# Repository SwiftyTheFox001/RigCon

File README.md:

# RigCon
Extension Board for the ClockworkPI uConsole to connect ham radio equiptment

## Features
- Rig Interface equal to the DigiRig
 - Audio interface + PTT (2,5mm Audio Jack)
 - UART interface (2,5mm Audio Jack)
- Additional external USB-C Port (500mA max)
- RTC with Backup Battery (CR1220)

## Production

### JLC PCB
The main PCB can be ordered nearly assembled via JLC PCB.
- PCB settings:
 - Load .zip file from the "Production" folder
 - PCB Thickness: 1mm
 - Surface Finish: ENIG (recommended because of the edge connector)
- Assembly:
 - use bom_JLC.csv and positions_JLC.csv from the  "Production" folder
 - Check rotation of chips THRICE! Rotate them so, that the pink dot is alligned with the white arrows.

### DigiKey
The battery clip, the two jacks and the USB port were ordered seperately from Digikey. See "Production/bom_complete.csv" for the product names or check in KiCAD directly.

These parts need to be soldered manually. Drop a bit of solder on the GND pin of the bettery clip to ensure that the pad is contacted properly.
 
## Setup the RTC
Follow the tutorial here: https://learn.adafruit.com/adding-a-real-time-clock-to-raspberry-pi/set-up-and-test-i2c
The used RTC is a pcf8523!

## Version History
### v1.1
Fixes of v1.0 applied to schematic, not re-ordered YET

Changes from RigCon version 1.0 to 1.1:
- changed clock crystal footprint
- removed I2C pullup resistor footprints (was DNP before)
- removed unneccessary load caps for clock crystal (RTC has internal ones)
- changed cap value on CM108B pin 37 to 10uF (NECESSARY!)
- removed GND connectrio on CM108B pin 16 SDIN (optional, simplified)

Added directory FrontPanel/ with dxf, openSCAD and stl files
Added Schematic to main dir
Added Render Pic of PCB to main dir

### v1.0
First ordered version.

## This work is based on other projects!
[DigiRig-mobile](https://github.com/softcomplex/Digirig-Mobile) ([v1.9](https://github.com/softcomplex/Digirig-Mobile/tree/6721ff3781d7879b822c3f6550d4fcae7a4c0a2a)) (GNU GPL v3)
To provide an audio, ptt and uart interface for digital modes for ham radio. The CM108 was replaced with an CM108B and the 2-port USB controller was replaced with a 4-port USB controller to accomodate the additional external USB Port. The pinout of the audio jacks, solder pads for configuration and test pins were reused 1:1 to allow an easy reuse of exisiting peripherals and support for a wide range of transceivers.

[uconsole-expansion-card-template-kicad](https://github.com/PotatoMania/uconsole-expansion-card-template-kicad) ([used Version](https://github.com/PotatoMania/uconsole-expansion-card-template-kicad/tree/a174627fb24a4a155137b862d881c7e6f08ff017)) (CC BY-SA 4.0) 
PCB Outline, speakers, M.2 connector and mounting hole placements. I Changed to shape of mounting holes and the speaker pads, but all measurements provided by the original were correct.

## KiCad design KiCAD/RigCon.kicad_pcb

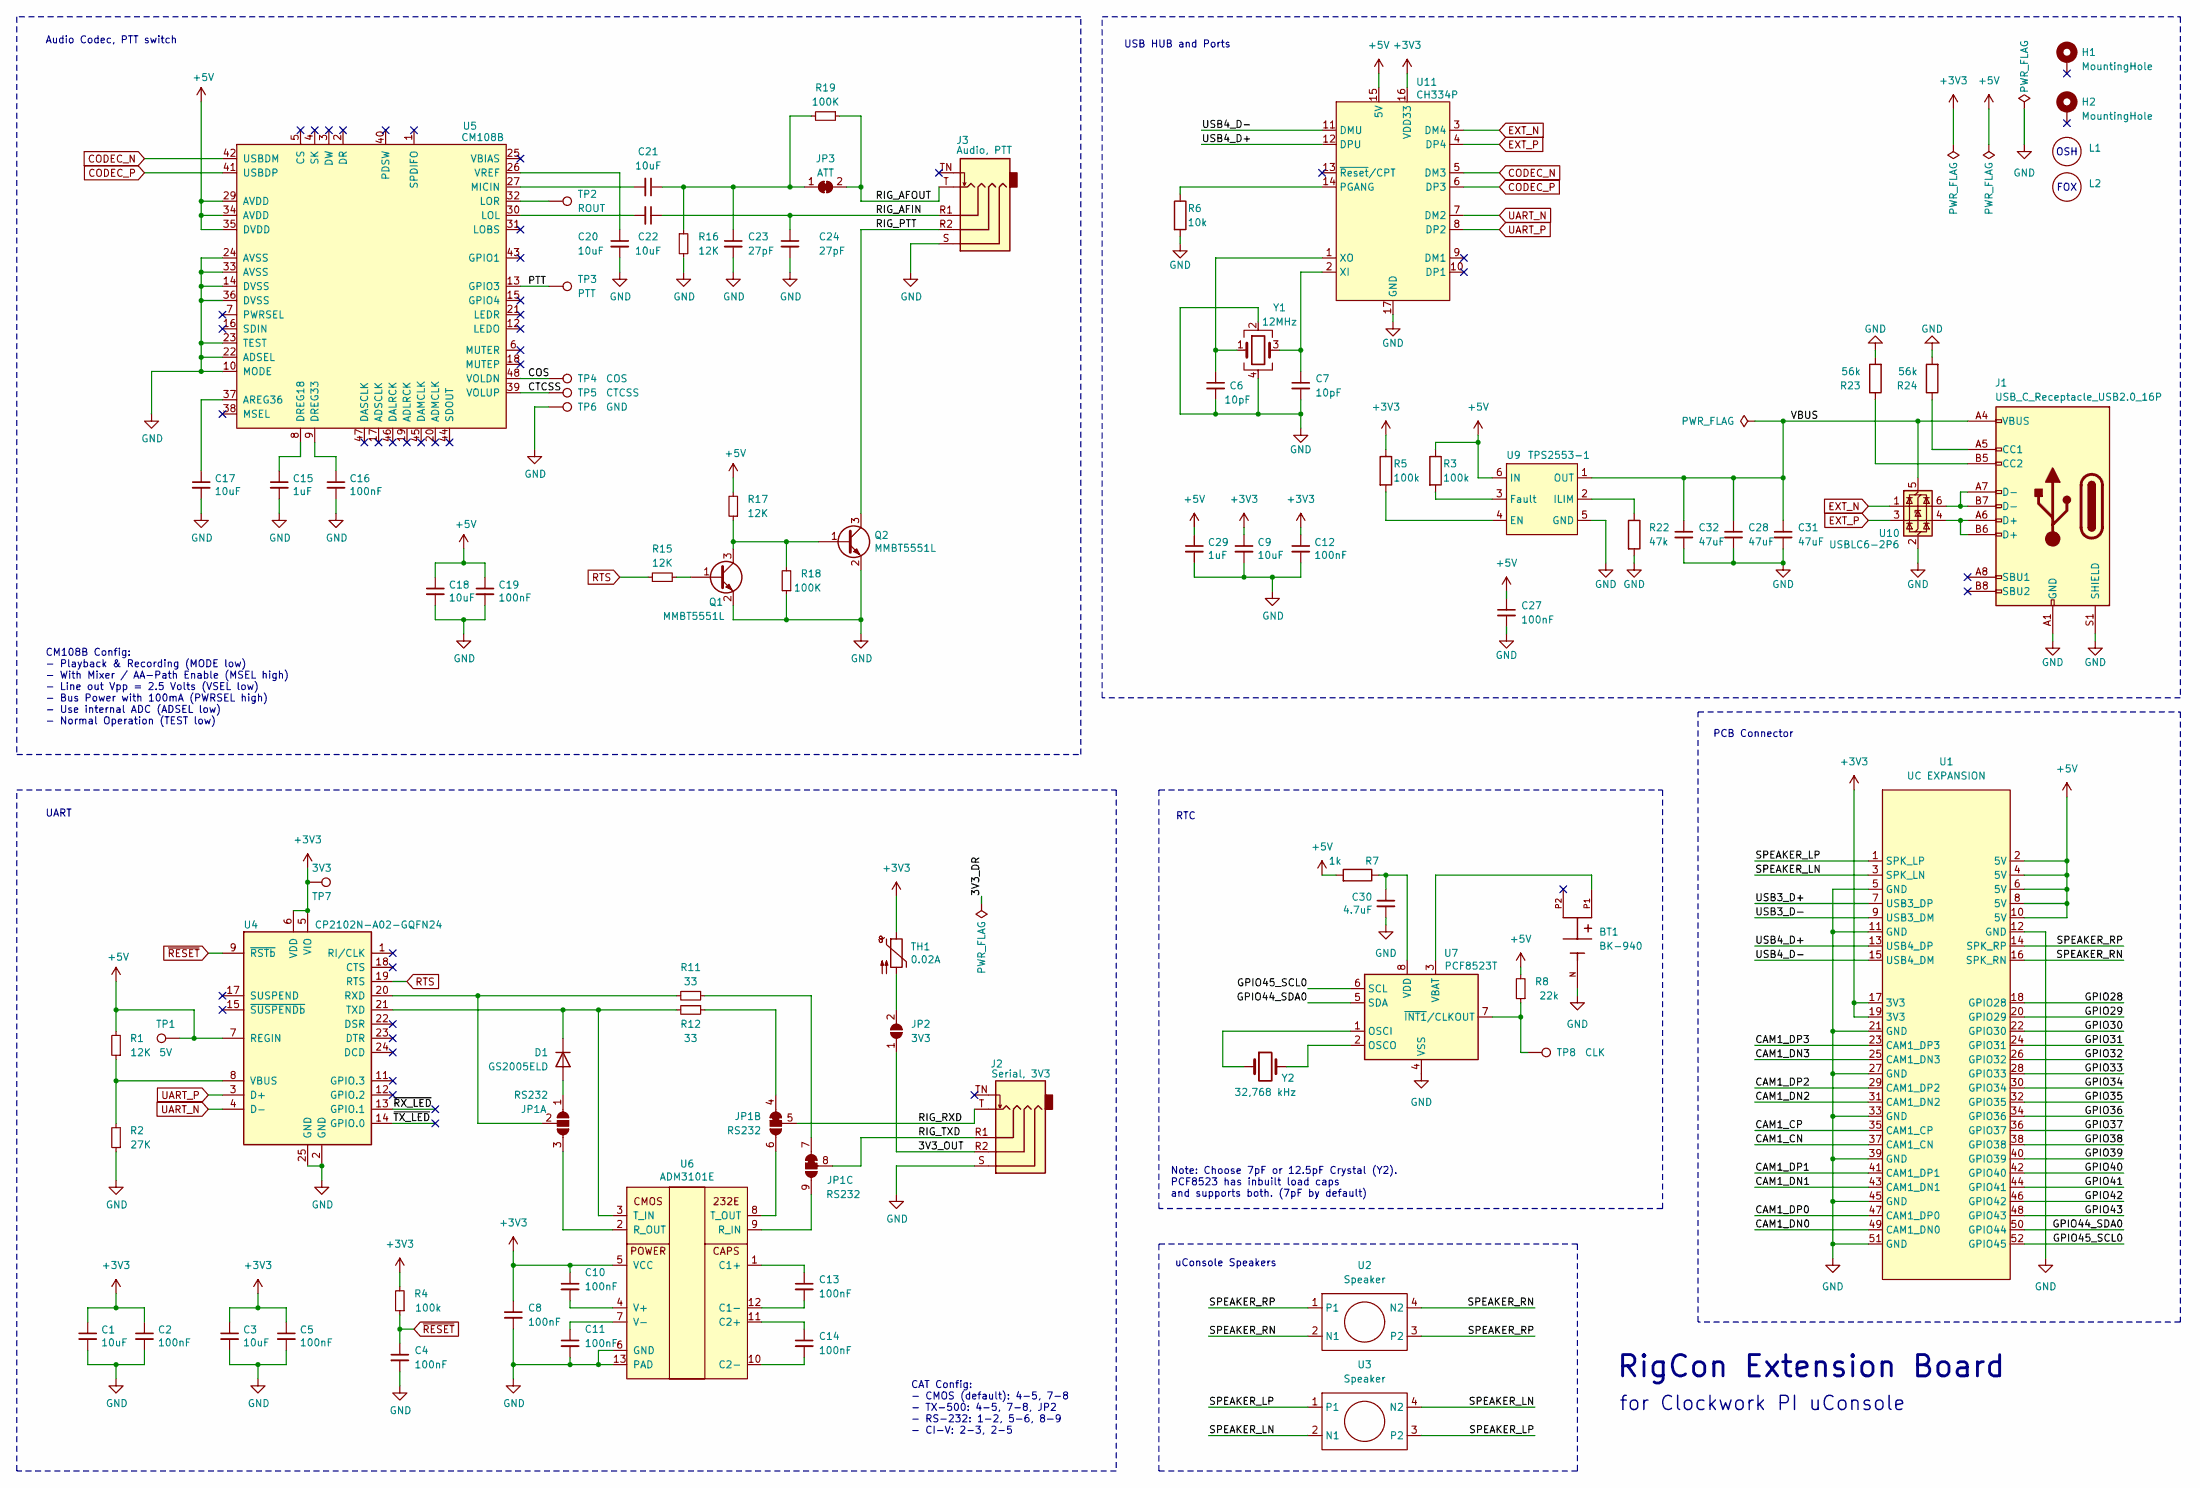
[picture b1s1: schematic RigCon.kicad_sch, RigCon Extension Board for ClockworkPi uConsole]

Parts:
BT1: BK-940; MPD_BK-940; PARTREV 04/15/21; DigiKeyNr BK-940
C1, C3, C9, C17, C18, C20, C21, C22: 10uF; C_0402_1005Metric; LCSC C15525
C2, C4, C5, C8, C10, C11, C12, C13, C14, C16, C19, C27: 100nF; C_0402_1005Metric; LCSC C1525
C6, C7: 10pF; C_0402_1005Metric; LCSC C1557
C15, C29: 1uF; C_0402_1005Metric; LCSC C52923
C23, C24: 27pF; C_0402_1005Metric; LCSC C1557
C28, C31, C32: 47uF; C_0805_2012Metric; LCSC C16780
C30: 4.7uF; C_0402_1005Metric; LCSC C23733
D1: GS2005ELD; D_SOD-923; LCSC C91106
H1, H2: MountingHole; MountingHole_5mm_Pad_Via
J1: USB_C_Receptacle_USB2.0_16P; USB-4520-03-X-A; DigiKeyNr USB4520-03-1-A
J2, J3: PJ-320A; SJ2-25774x-SMT; DigiKeyNr CP-SJ2-25774A-SMT
JP1: RS232; SolderJumper9-BCu
JP2: 3V3; SolderJumper2-BCu
JP3: ATT; SolderJumper-BCu-Bridged
L1: OSHW-Symbol_6.7x6mm_SilkScreen
L2: Logo_Fox
Q1, Q2: MMBT5551L; SOT-23; LCSC C41095
R1, R15, R16, R17: 12K; R_0402_1005Metric; LCSC C25752
R2: 27K; R_0402_1005Metric
R3, R4, R5: 100k; R_0402_1005Metric
R6: 10k; R_0402_1005Metric
R7: 1k; R_0402_1005Metric
R8: 22k; R_0402_1005Metric
R11, R12: 33; R_0402_1005Metric
R18, R19: 100K; R_0402_1005Metric
R22: 47k; R_0402_1005Metric
R23, R24: 56k; R_0402_1005Metric
TH1: 0.02A; R_0603_1608Metric; LCSC C914089
TP1: 5V; TestPoint_THTPad_D1.5mm_Drill0.7mm
TP2: ROUT; TestPoint_THTPad_D1.5mm_Drill0.7mm
TP3: PTT; TestPoint_THTPad_D1.5mm_Drill0.7mm
TP4: COS; TestPoint_THTPad_D1.5mm_Drill0.7mm
TP5: CTCSS; TestPoint_THTPad_D1.5mm_Drill0.7mm
TP6: GND; TestPoint_THTPad_D1.5mm_Drill0.7mm
TP7: 3V3; TestPoint_THTPad_D1.5mm_Drill0.7mm
TP8: CLK; TestPoint_THTPad_D1.5mm_Drill0.7mm
U1: UC EXPANSION; edge-minipcie
U2, U3: Speaker; speaker pads
U4: CP2102N-A02-GQFN24; QFN-24-1EP_4x4mm_P0.5mm_EP2.6x2.6mm; LCSC C969151
U5: CM108B; LQFP-48_7x7mm_P0.5mm; LCSC C371347
U6: ADM3101E; QFN-12-1EP_3x3mm_P0.51mm_EP1.45x1.45mm; LCSC C514336
U7: PCF8523T; SOIC-8_3.9x4.9mm_P1.27mm; LCSC C2651516
U9: TPS2553-1; WSON-6-1EP_2x2mm_P0.65mm_EP1x1.6mm; LCSC C411878
U10: USBLC6-2P6; SOT-666; LCSC C15999
U11: CH334P; QFN-16-1EP_3x3mm_P0.5mm_EP1.7x1.7mm_ThermalVias; LCSC C5373042
Y1: 12MHz; Crystal_SMD_3225-4Pin_3.2x2.5mm; LCSC C20617575
Y2: 32,768 kHz; Crystal_SMD_3215-2Pin_3.2x1.5mm; LCSC C97604

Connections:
+3V3: C1.1, C2.1, C3.1, C5.1, C8.1, C9.1, C10.1, C12.1, R4.2, R5.1, TH1.1, TP7.1, U1.17 (3V3), U1.19 (3V3), U4.5 (VIO), U4.6 (VDD), U6.5 (VCC), U11.16 (VDD33)
+5V: C18.1, C19.1, C27.1, C29.1, R1.2, R3.1, R7.2, R8.2, R17.2, TP1.1, U1.2 (5V), U1.4 (5V), U1.6 (5V), U1.8 (5V), U1.10 (5V), U4.7 (REGIN), U5.29 (AVDD), U5.34 (AVDD), U5.35 (DVDD), U9.6 (IN), U11.15 (5V)
/3V3_OUT: J2.R2, JP2.1 (A)
/CAM1_CN: U1.37 (CAM1_CN)
/CAM1_CP: U1.35 (CAM1_CP)
/CAM1_DN0: U1.49 (CAM1_DN0)
/CAM1_DN1: U1.43 (CAM1_DN1)
/CAM1_DN2: U1.31 (CAM1_DN2)
/CAM1_DN3: U1.25 (CAM1_DN3)
/CAM1_DP0: U1.47 (CAM1_DP0)
/CAM1_DP1: U1.41 (CAM1_DP1)
/CAM1_DP2: U1.29 (CAM1_DP2)
/CAM1_DP3: U1.23 (CAM1_DP3)
/COS: TP4.1, U5.48 (VOLDN)
/CTCSS: TP5.1, U5.39 (VOLUP)
/GPIO28: U1.18 (GPIO28)
/GPIO29: U1.20 (GPIO29)
/GPIO30: U1.22 (GPIO30)
/GPIO31: U1.24 (GPIO31)
/GPIO32: U1.26 (GPIO32)
/GPIO33: U1.28 (GPIO33)
/GPIO34: U1.30 (GPIO34)
/GPIO35: U1.32 (GPIO35)
/GPIO36: U1.34 (GPIO36)
/GPIO37: U1.36 (GPIO37)
/GPIO38: U1.38 (GPIO38)
/GPIO39: U1.40 (GPIO39)
/GPIO40: U1.42 (GPIO40)
/GPIO41: U1.44 (GPIO41)
/GPIO42: U1.46 (GPIO42)
/GPIO43: U1.48 (GPIO43)
/GPIO44_SDA0: U1.50 (GPIO44), U7.5 (SDA)
/GPIO45_SCL0: U1.52 (GPIO45), U7.6 (SCL)
/PTT: TP3.1, U5.13 (GPIO3)
/RIG_AFIN: C22.1, C24.1, J3.R1
/RIG_AFOUT: J3.T, JP3.2 (B), R19.1
/RIG_PTT: J3.R2, Q2.3 (C)
/RIG_RXD: J2.T, JP1.5 (B)
/RIG_TXD: J2.R1, JP1.8 (B)
/SPEAKER_LN: U1.3 (SPK_LN), U3.2 (N1), U3.4 (N2)
/SPEAKER_LP: U1.1 (SPK_LP), U3.1, U3.3 (P2)
/SPEAKER_RN: U1.16 (SPK_RN), U2.2 (N1), U2.4 (N2)
/SPEAKER_RP: U1.14 (SPK_RP), U2.1, U2.3 (P2)
/USB3_D+: U1.7 (USB3_DP)
/USB3_D-: U1.9 (USB3_DM)
/USB4_D+: U1.13 (USB4_DP), U11.12 (DPU)
/USB4_D-: U1.15 (USB4_DM), U11.11 (DMU)
/VBUS: C28.1, C31.1, C32.1, J1.A4 (VBUS), J1.A9 (VBUS), J1.B4 (VBUS), J1.B9 (VBUS), U9.1 (OUT), U10.5 (VBUS)
/~RX_LED: U4.13 (GPIO.1)
/~TX_LED: U4.14 (GPIO.0)
CODEC_N: U5.42 (USBDM), U11.5 (DM3)
CODEC_P: U5.41 (USBDP), U11.6 (DP3)
EXT_N: U10.1 (I/O1), U11.3 (DM4)
EXT_P: U10.3 (I/O2), U11.4 (DP4)
GND: BT1.N, C1.2, C2.2, C3.2, C4.2, C5.2, C6.2, C7.2, C8.2, C9.2, C11.2, C12.2, C15.2, C16.2, C17.2, C18.2, C19.2, C20.2, C23.2, C24.2, C27.2, C28.2, C29.2, C30.2, C31.2, C32.2, J1.A1 (GND), J1.A12 (GND), J1.B1 (GND), J1.B12 (GND), J1.S1 (SHIELD), J2.S, J3.S, Q1.2 (E), Q2.2 (E), R2.1, R6.2, R16.2, R18.1, R22.2, R23.2, R24.2, TP6.1, U1.5 (GND), U1.11 (GND), U1.12 (GND), U1.21 (GND), U1.27 (GND), U1.33 (GND), U1.39 (GND), U1.45 (GND), U1.51 (GND), U4.2 (GND), U4.25 (GND), U5.10 (MODE), U5.14 (DVSS), U5.22 (ADSEL), U5.23 (TEST), U5.24 (AVSS), U5.33 (AVSS), U5.36 (DVSS), U6.6 (GND), U6.13 (PAD), U7.4 (VSS), U9.5 (GND), U9.7 (GND), U10.2 (GND), U11.17 (GND), Y1.2, Y1.4
unnamed: D1.2 (A), JP1.1 (A)
unnamed: D1.1 (K), R12.2, U4.21 (TXD), U6.3 (T_IN)
unnamed: J1.A5 (CC1), R24.1
unnamed: J1.B5 (CC2), R23.1
unnamed: J1.A6 (D+), J1.B6 (D+), U10.4 (I/O2)
unnamed: J1.A7 (D-), J1.B7 (D-), U10.6 (I/O1)
unnamed: JP1.2 (B), R11.2, U4.20 (RXD)
unnamed: JP1.3 (C), U6.2 (R_OUT)
unnamed: JP1.4 (A), R12.1
unnamed: JP1.6 (C), U6.8 (T_OUT)
unnamed: JP1.7 (A), R11.1
unnamed: JP1.9 (C), U6.9 (R_IN)
unnamed: JP2.2 (B), TH1.2
unnamed: C21.1, C23.1, JP3.1 (A), R16.1, R19.2
unnamed: Q1.1 (B), R15.2
unnamed: Q1.3 (C), Q2.1 (B), R17.1, R18.2
unnamed: R1.1, R2.2, U4.8 (VBUS)
unnamed: C17.1, U5.37 (AREG36)
unnamed: C15.1, U5.8 (DREG18)
unnamed: C16.1, U5.9 (DREG33)
unnamed: C22.2, U5.30 (LOL)
unnamed: TP2.1, U5.32 (LOR)
unnamed: C21.2, U5.27 (MICIN)
unnamed: C20.1, U5.26 (VREF)
unnamed: C13.1, U6.1 (C1+)
unnamed: C13.2, U6.12 (C1-)
unnamed: C14.1, U6.11 (C2+)
unnamed: C14.2, U6.10 (C2-)
unnamed: C10.2, U6.4 (V+)
unnamed: C11.1, U6.7 (V-)
unnamed: U7.1 (OSCI), Y2.1
unnamed: U7.2 (OSCO), Y2.2
unnamed: BT1.P1, U7.3 (VBAT)
unnamed: C30.1, R7.1, U7.8 (VDD)
unnamed: R8.1, TP8.1, U7.7 (~INT1/CLKOUT)
unnamed: R5.2, U9.4 (EN)
unnamed: R3.2, U9.3 (Fault)
unnamed: R22.1, U9.2 (ILIM)
unnamed: R6.1, U11.14 (PGANG)
unnamed: C7.1, U11.2 (XI), Y1.3
unnamed: C6.1, U11.1 (XO), Y1.1
RTS: R15.1, U4.19 (RTS)
UART_N: U4.4 (D-), U11.7 (DM2)
UART_P: U4.3 (D+), U11.8 (DP2)
~RESET: C4.1, R4.1, U4.9 (~RSTb)

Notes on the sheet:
PCB Connector
UART
Note: Choose 7pF or 12.5pF Crystal (Y2). PCF8523 has inbuilt load caps and supports both. (7pF by default)
Audio Codec, PTT switch
CAT Config: - CMOS (default): 4-5, 7-8 - TX-500: 4-5, 7-8, JP2 - RS-232: 1-2, 5-6, 8-9 - CI-V: 2-3, 2-5
for Clockwork PI uConsole
uConsole Speakers
OSH
FOX
RigCon Extension Board
USB HUB and Ports
CM108B Config: - Playback & Recording (MODE low) - With Mixer / AA-Path Enable (MSEL high) - Line out Vpp = 2.5 Volts (VSEL low) - Bus Power with 100mA (PWRSEL high) - Use internal ADC (ADSEL low) - Normal Operation (TEST low)
RTC

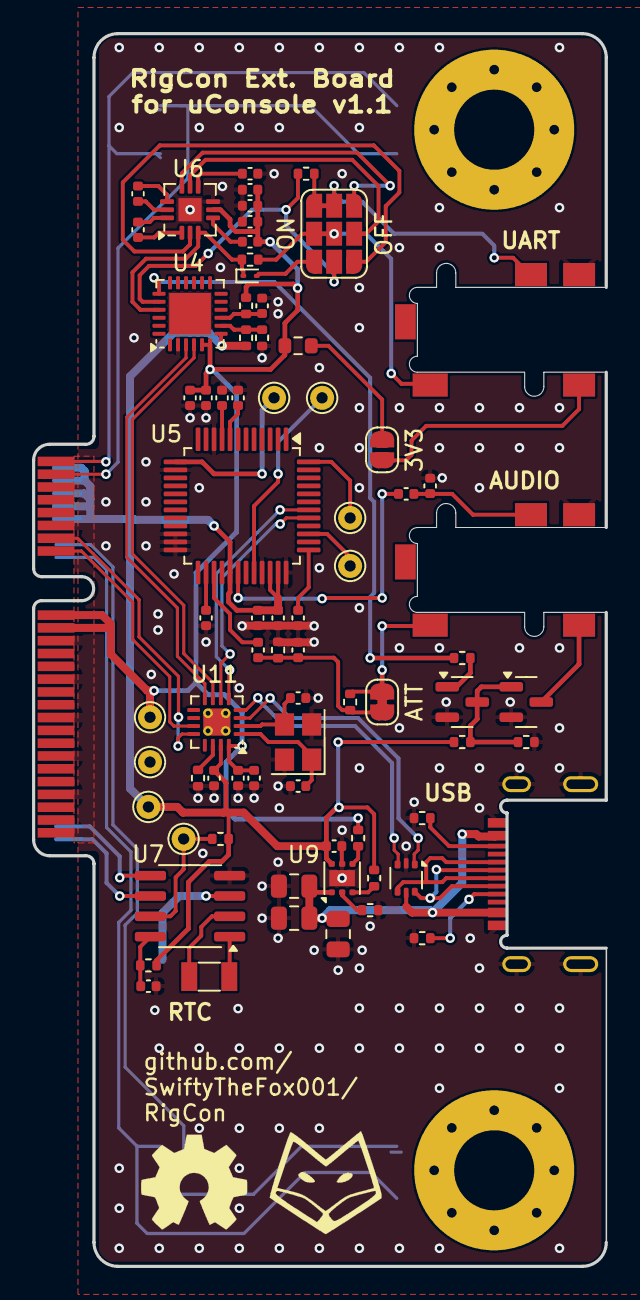
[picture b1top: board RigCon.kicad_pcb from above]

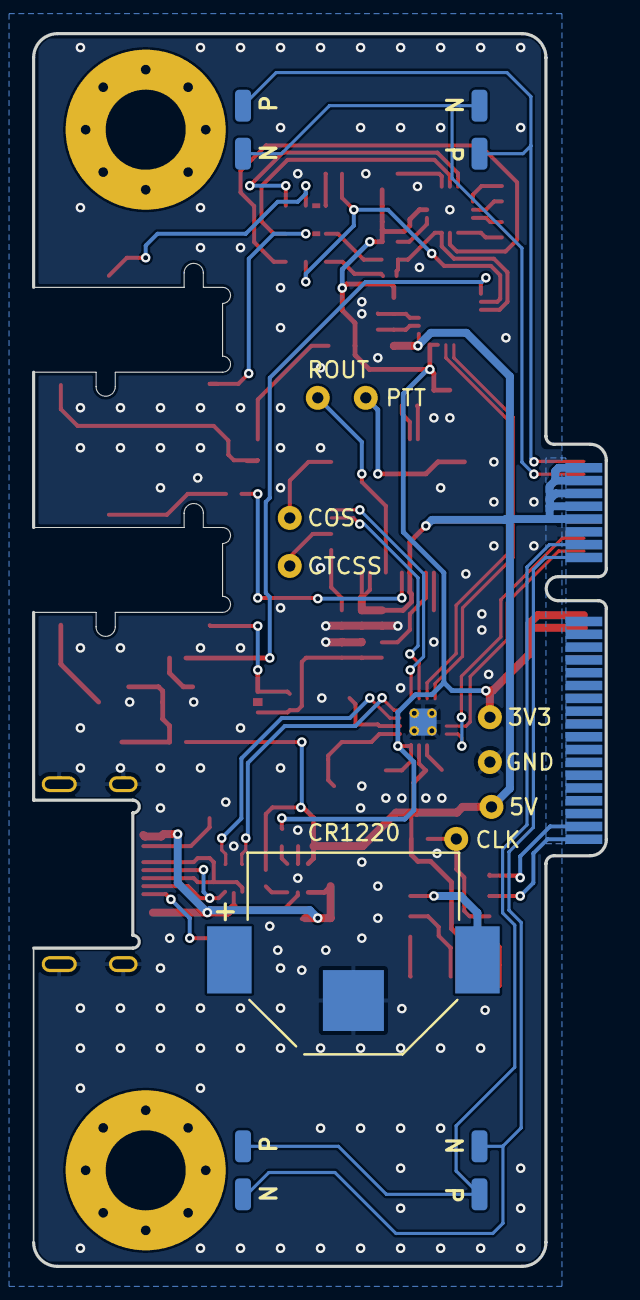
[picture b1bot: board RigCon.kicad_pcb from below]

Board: 2 copper layers, 35.8 x 77.0 mm, 83 parts (6 on the bottom side), 70 nets.

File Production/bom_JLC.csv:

Comment,Designator,Footprint,LCSC,Quantity
1k,R7,R_0402_1005Metric,C11702,1
100nF,"C10,C11,C12,C13,C14,C16,C19,C2,C27,C4,C5,C8",C_0402_1005Metric,C1525,12
10uF,"C1,C17,C18,C20,C21,C22,C3,C9",C_0402_1005Metric,C15525,8
27pF,"C23,C24,C6,C7",C_0402_1005Metric,C1557,4
USBLC6-2P6,U10,SOT-666,C15999,1
47uF,"C28,C31,C32",C_0805_2012Metric,C16780,3
12MHz,Y1,Crystal_SMD_3225-4Pin_3.2x2.5mm,C20617575,1
4.7uF,C30,C_0402_1005Metric,C23733,1
33,"R11,R12",R_0402_1005Metric,C25105,2
100K,"R18,R19,R3,R4,R5",R_0402_1005Metric,C25741,5
10k,R6,R_0402_1005Metric,C25744,1
12K,"R1,R15,R16,R17",R_0402_1005Metric,C25752,4
22k,R8,R_0402_1005Metric,C25768,1
27K,R2,R_0402_1005Metric,C25771,1
47k,R22,R_0402_1005Metric,C25792,1
56k,"R23,R24",R_0402_1005Metric,C25796,2
PCF8523T,U7,SOIC-8_3.9x4.9mm_P1.27mm,C2651516,1
CM108B,U5,LQFP-48_7x7mm_P0.5mm,C371347,1
MMBT5551L,"Q1,Q2",SOT-23,C41095,2
TPS2553-1,U9,WSON-6-1EP_2x2mm_P0.65mm_EP1x1.6mm,C411878,1
ADM3101E,U6,QFN-12-1EP_3x3mm_P0.51mm_EP1.45x1.45mm,C514336,1
1uF,"C15,C29",C_0402_1005Metric,C52923,2
CH334P,U11,QFN-16-1EP_3x3mm_P0.5mm_EP1.7x1.7mm_ThermalVias,C5373042,1
GS2005ELD,D1,D_SOD-923,C91106,1
0.02A,TH1,R_0603_1608Metric,C914089,1
CP2102N-A02-GQFN24,U4,QFN-24-1EP_4x4mm_P0.5mm_EP2.6x2.6mm,C969151,1
"32,768 kHz",Y2,Crystal_SMD_3215-2Pin_3.2x1.5mm,C97604,1

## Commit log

2025-02-26 First commit with KiCAD project and datasheets
2025-02-26 Renamed KiCAD Project to "RigCon"
2025-02-26 Updated PCB: routing added fox logo correct symbol for mounting hole with pad
2025-02-26 Removed DigiRig Footprint Library Added github URL on silkscreen
2025-02-26 Changed Readme.md
2025-02-26 Fixed Errors in Labels excluded parts from position file and bom
2025-02-27 Version of prototype order (v1.0)
    Updated a few Texts and Order Numbers
    Updated TPS2553 to TPS2553-1 (Latched version)
2025-03-22 Changes from RigCon version 1.0 to 1.1:
    - changed clock crystal footprint
    - removed I2C pullup resistor footprints (was DNP before)
    - removed unneccessary load caps for clock crystal (RTC has internal ones)
    - changed cap value on CM108B pin 37 to 10uF (NECESSARY!)
    - removed GND connectrio on CM108B pin 16 SDIN (optional, simplified)
    Added directory FrontPanel/ with dxf, openSCAD and stl files
2025-03-22 PCB: Minor Changes Updated Document Information (Header, Version, Date)
2025-03-22 removed production Folder (not up to date yet)
2025-03-23 - Added Gerber, BOM & part positions for production - improved README
2025-04-27 Added missing BOM files that were ommited by the .gitignore
2025-04-29 Fix JLCPCB CPL rotation, update KiCad version
    Re-generated JLCPCB component placement file using kicad-jlcpcb-tools.
    Fixed components rotation so it appears correctly when loaded in JLCPCB.
    Update KiCad project to version 9.0.1.
